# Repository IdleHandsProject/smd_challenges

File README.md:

# smd_challenges
A place for all of the SMD challenges I will be creating.

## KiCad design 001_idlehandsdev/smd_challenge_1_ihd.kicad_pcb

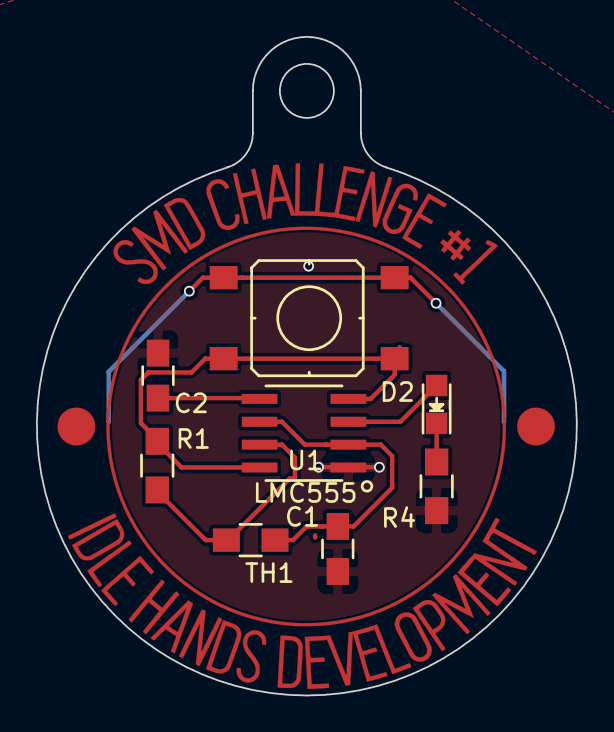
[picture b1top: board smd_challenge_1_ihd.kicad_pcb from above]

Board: 2 copper layers, 30.0 x 36.6 mm, 11 parts (1 on the bottom side), 8 nets.

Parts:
BT1: Battery; CoinCellHolder_SM
C1: 47uF; C_0805_HandSoldering
C2: 10nF; C_0805_HandSoldering
D2: LED; LED-0805
LogoCu: CU; smdc1_cu
LogoMask: MASK; smdc1_mask
R1: 15K; R_0805_HandSoldering
R4: 1K; R_0805_HandSoldering
SW1: SPST; Button_CKN9112CT-ND
TH1: TH_PTH; R_0805_HandSoldering
U1: LMC555; LMC555CMX

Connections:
+BATT: BT1.2, SW1.1
GND: BT1.1, C1.2, C2.2, R4.2, U1.1
unnamed: C1.1, TH1.2, U1.2, U1.6
unnamed: C2.1, U1.5
unnamed: D2.1, R4.1
unnamed: D2.2, U1.3
unnamed: R1.1, SW1.2, U1.4, U1.8
unnamed: R1.2, TH1.1, U1.7

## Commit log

2017-10-17 change folder name
2017-10-20 added next 10 projects

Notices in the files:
parts and their libraries:
Copyright 2016 Accelerated Designs. All rights reserved.
